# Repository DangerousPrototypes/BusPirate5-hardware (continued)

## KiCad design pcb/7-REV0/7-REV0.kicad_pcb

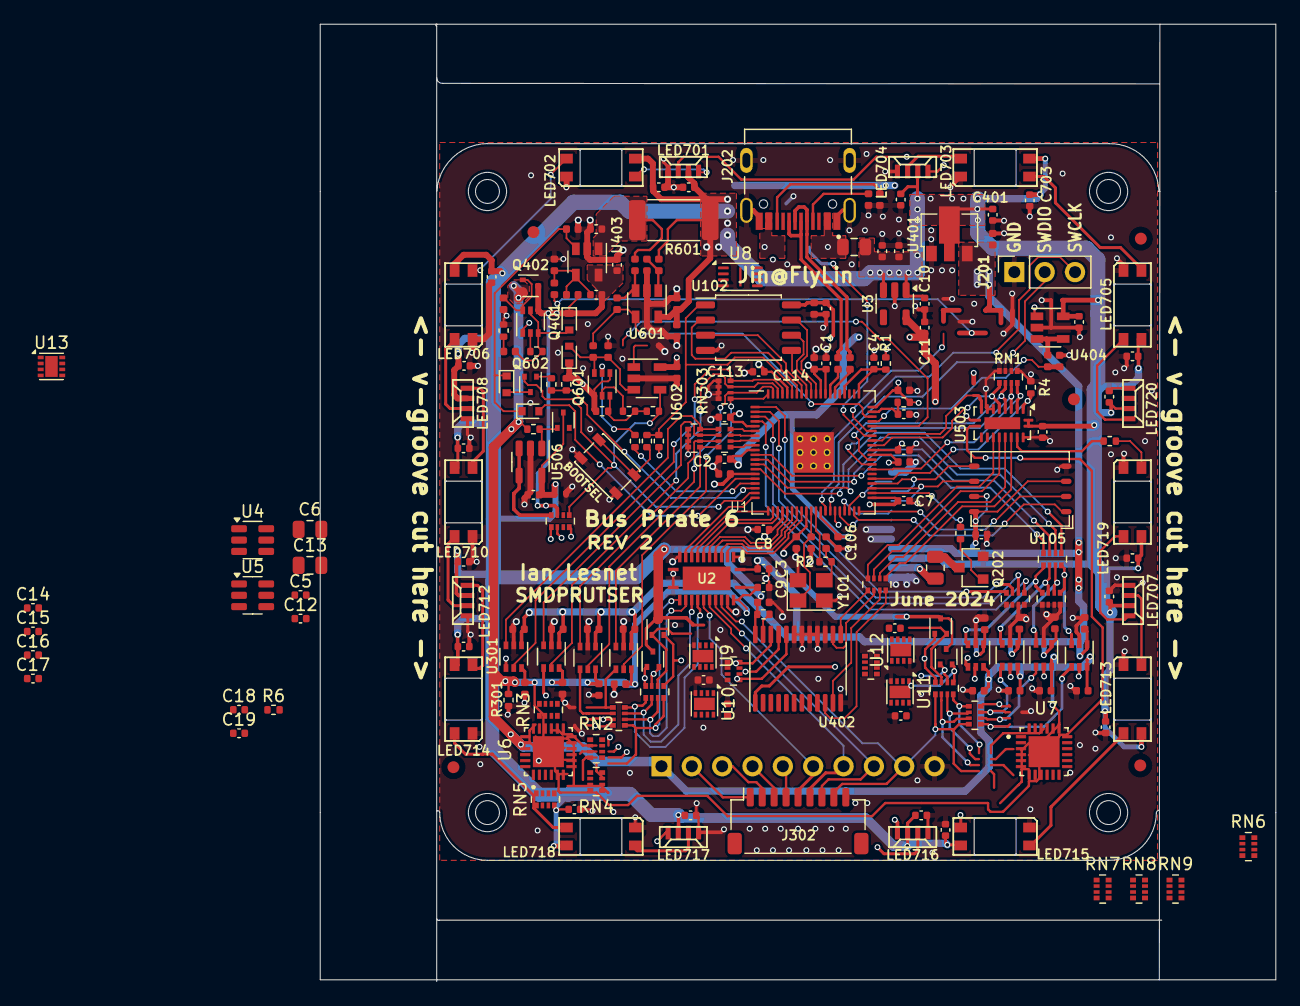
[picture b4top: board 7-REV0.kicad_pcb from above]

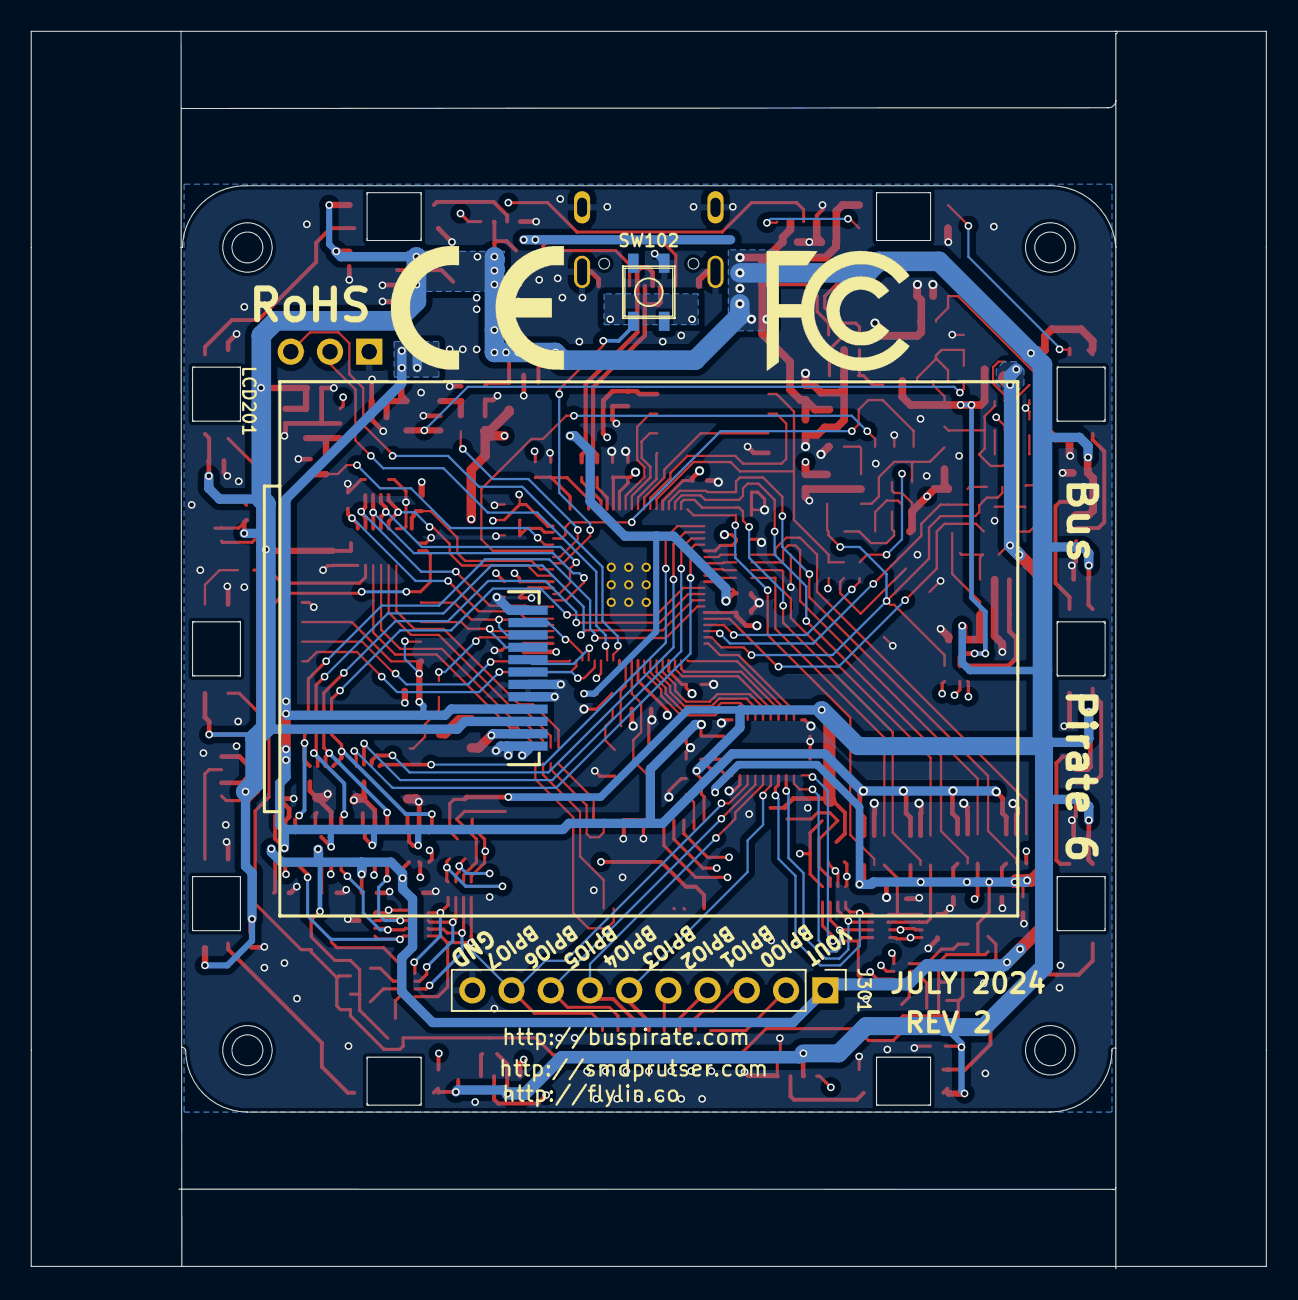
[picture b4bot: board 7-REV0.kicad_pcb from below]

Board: 4 copper layers, 80.0 x 80.0 mm, 232 parts (5 on the bottom side), 210 nets.

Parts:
C1, C2, C3, C5, C7, C8, C9, C12, C14, C15, C16, C17, C18, C103, C110, C111, C112, C113, C114, C115, C116, C117, C118, C121, C301, C302, C303, C304, C305, C306, C307, C308, C309, C310, C311, C312, C313, C314, C315, C316, C403, C406, C503, C506, C507, C508, C509, C510, C602, C605, C701, C702, C703, C704, C705, C706, C707, C708, C710, C712, C713, C714, C715, C716, C717, C718, C719, C720: 0.1uF; C_0402_1005Metric
C4, C19, C104, C109, C601: 2.2uF; C_0402_1005Metric
C6, C13: 10uF; C_0805_2012Metric
C10, C11, C201, C202, C401, C402, C404, C407: 4.7uF; C_0402_1005Metric
C105, C106: 15pF; C_0402_1005Metric
C408: 120pF; C_0402_1005Metric
C603: DNF; C_0402_1005Metric
D401, D601, D602, D603: 1N4148WT; D_SOD-523
D500, D501, D502, D503, D504: BAS40T-05; SOT-523
FID1, FID2, FID3, FID4, FID5: Fiducial; Fiducial_1mm_Mask2mm
H1, H2, H3, H4: MountingHole; MountingHole_3.2mm_M3
J201: Conn_01x03; PinSocket_1x03_P2.54mm_Vertical
J202: TYPE-C-31-M-12; HRO_TYPE-C-31-M-12
J301: Conn_01x10; PinHeader_1x10_P2.54mm_Vertical
J302: Conn_01x09; JST_SH_SM09B-SRSS-TB_1x09-1MP_P1.00mm_Horizontal
L201: CBW201209U300T; L_0805_2012Metric
LCD201: TFT_20_QT200H1201
LED701, LED704, LED707, LED708, LED712, LED716, LED717, LED720: SK6812-side-a_b
LED702, LED703, LED705, LED706, LED710, LED713, LED714, LED715, LED718, LED719: SK6812-mini-e
Q202: MMBT7002K; SOT-23
Q401: BCM857; SOT-363_SC-70-6
Q402, Q602: BC2301T 2.8A; SOT-523
Q601: MMDT3906; SOT-363_SC-70-6
R1: 10R; R_0402_1005Metric
R2, R101, R502, R602, R603: 1K; R_0402_1005Metric
R4, R6, R319, R401, R412: 100K; R_0402_1005Metric
R102: DNF; R_0402_1005Metric
R103, R208, R608, R612: 200R; R_0402_1005Metric
R201, R204: 5.1K; R_0402_1005Metric
R202, R203: 22R; R_0402_1005Metric
R209: 33R; R_0805_2012Metric
R301, R406, R407, R410, R606, R609, R610, R611, R613: 10K; R_0402_1005Metric
R320: 510R; R_0402_1005Metric
R403: 102K; R_0402_1005Metric
R404: 133K; R_0402_1005Metric
R405, R408, R409, R604, R605: 33K; R_0402_1005Metric
R601: 0R2; R_2512_6332Metric_Pad1.40x3.35mm_HandSolder
RN1, RN302, RN303, RN307, RN308, RN317, RN318: 100K; R_Array_Convex_4x0402
RN2, RN8: 1M; R_Array_Convex_4x0402
RN3, RN9: 10K; R_Array_Convex_4x0402
RN4, RN7: 4.7K; R_Array_Convex_4x0402
RN5, RN6: 2.2K; R_Array_Convex_4x0402
RN301, RN306: 330R; R_Array_Convex_4x0402
RN305, RN309: 120R; R_Array_Convex_4x0402
RN315, RN400, RN401, RN402: 510R; R_Array_Convex_4x0402
SW101: TS3425BA 098 2.5H 250gf; SW_SPST_PTS810
SW102: TS3315A 250gf 025; GT-TC026X-HXXX-LX
U1: RP2350B; qfn80
U2: 74LVC8T245BQ; NXP-DHVQFN24
U3: TLV74311PDBVR; SOT-23-5
U4, U5: MCP4725xxx-xCH; SOT-23-6
U6, U7: TCA6416RTWT; QFN50P400X400X80-25N
U8: APS6404L-3SQR-ZR; Winbond_USON-8-1EP_3x2mm_P0.5mm_EP0.2x1.6mm
U9, U10, U11, U12, U13: LM358_DFN; DFN-8-1EP_2x2mm_P0.5mm_EP1.05x1.75mm
U102: W25Q128JVSIQ; SOP-8_5.28x5.23mm_P1.27mm
U105: MT29F1G01ABAFDWB; U-PDFN-8
U301, U302, U303, U304, U305, U306, U307, U308: AiP74LVC1T45GC363.TR; SOT-363_SC-70-6
U401: ME6211A33PG-N; SOT-89-3
U402: CD4067; TSSOP-24_4.4x7.8mm_P0.65mm
U403: AP2127; SOT-23-5
U404, U506: LMV321; SOT-23-5
U503: 74HCT245BQ; DHVQFN-20-1EP_2.5x4.5mm_P0.5mm_EP1x3mm
U601: GS321A-TR; SOT-23-5
U602: GSV331-TR; SOT-23-5
Y101: ABM8-272-T3; Crystal_SMD_3225-4Pin_3.2x2.5mm
logo1: fcc_logo; logo_fcc
logo2: ce_logo; CE-Logo_11.2x8mm_SilkScreen

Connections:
+1V1: C2.1, C11.1, C117.1, C118.1, U1.10 (DVDD), U1.32 (DVDD), U1.51 (DVDD), U3.5 (VOUT)
+3V3: C1.1, C3.2, C5.1, C6.1, C7.1, C8.1, C12.1, C13.1, C15.2, C17.2, C18.1, C19.1, C103.1, C104.1, C110.1, C111.1, C112.1, C113.1, C114.1, C115.1, C116.1, C121.1, C301.2, C302.2, C303.2, C307.2, C308.2, C309.2, C313.2, C314.2, C402.1, C605.1, D601.1 (K), LCD201.4 (VCC), Q601.1 (E1), Q601.4 (E2), R1.1, R6.1, R102.1, R103.1, R609.1, R613.1, U1.5 (IOVDD), U1.15 (IOVDD), U1.24 (IOVDD), U1.29 (IOVDD), U1.35 (RUN), U1.41 (IOVDD), U1.50 (IOVDD), U1.60 (IOVDD), U1.68 (USB_OTP_VDD), U1.69 (QSPI_IOVDD), U1.76 (IOVDD), U2.1 (VCCA), U4.3 (VDD), U5.3 (VDD), U5.6 (A0), U6.23 (VCCI), U7.18 (ADDR), U7.23 (VCCI), U8.8 (VCC), U102.8 (VCC), U105.3 (WP/IO2), U105.7 (HOLD/IO3), U105.8 (VCC), U301.1 (VCCA), U302.1 (VCCA), U303.1 (VCCA), U304.1 (VCCA), U305.1 (VCCA), U306.1 (VCCA), U307.1 (VCCA), U308.1 (VCCA), U401.3 (VOUT), U602.5 (V+)
+VUSB: C10.1, C201.2, C202.2, C401.1, C403.2, C406.1, C503.2, C506.1, C507.2, C508.2, C509.2, C510.2, C601.1, C602.2, C701.2, C702.2, C703.2, C704.2, C705.2, C706.2, C707.2, C708.2, C710.2, C712.2, C713.2, C714.2, C715.2, C716.2, C717.2, C718.2, C719.2, C720.2, D500.3, D501.3, D502.3, D503.3, D504.3, L201.1, LCD201.3 (LED-A), LED701.3 (VDD), LED702.1 (VDD), LED703.1 (VDD), LED704.3 (VDD), LED705.1 (VDD), LED706.1 (VDD), LED707.3 (VDD), LED708.3 (VDD), LED710.1 (VDD), LED712.3 (VDD), LED713.1 (VDD), LED714.1 (VDD), LED715.1 (VDD), LED716.3 (VDD), LED717.3 (VDD), LED718.1 (VDD), LED719.1 (VDD), LED720.3 (VDD), R320.2, R601.1, R602.2, U3.1 (VIN), U3.3 (~SHDN), U9.8 (V+), U10.8 (V+), U11.8 (V+), U12.8 (V+), U401.2 (VIN), U402.24 (VCC), U404.5 (V+), U503.1 (A->B), U503.20 (VCC), U506.5 (V+), U601.5 (V+)
AMUX_OUT: R406.2, R407.2, U1.57 (GPIO46_ADC6)
AMUX_S0: RN315.4 (R1.1), U402.10 (S0)
AMUX_S0_3V3: RN1.8 (R1.8), U1.47 (GPIO38), U503.3 (A1)
AMUX_S1: RN315.3 (R1.1), U402.11 (S1)
AMUX_S1_3V3: RN1.7 (R1.8), U1.48 (GPIO39), U503.4 (A2)
AMUX_S2: RN315.2 (R1.1), U402.14 (S2)
AMUX_S2_3V3: RN1.6 (R1.8), U1.49 (GPIO40_ADC0), U503.5 (A3)
AMUX_S3: RN315.1 (R1.1), U402.13 (S3)
AMUX_S3_3V3: RN1.5 (R1.8), U1.52 (GPIO41_ADC1), U503.6 (A4)
BPIO0: J301.2, J302.1, RN6.4 (R1.1), RN7.4 (R1.1), RN8.1 (R1.1), RN9.1 (R1.1), RN305.1 (R1.1), RN318.8 (R1.8), U2.14 (B8)
BPIO1: J301.3, J302.2, RN6.3 (R1.1), RN7.3 (R1.1), RN8.2 (R1.1), RN9.2 (R1.1), RN305.2 (R1.1), RN318.7 (R1.8), U2.15 (B7)
BPIO2: J301.4, J302.3, RN6.2 (R1.1), RN7.2 (R1.1), RN8.3 (R1.1), RN9.3 (R1.1), RN305.3 (R1.1), RN318.6 (R1.8), U2.16 (B6)
BPIO3: J301.5, J302.4, RN6.1 (R1.1), RN7.1 (R1.1), RN8.4 (R1.1), RN9.4 (R1.1), RN305.4 (R1.1), RN318.5 (R1.8), U2.17 (B5)
BPIO4: J301.6, J302.5, RN2.1 (R1.1), RN3.1 (R1.1), RN4.4 (R1.1), RN5.4 (R1.1), RN309.1 (R1.1), RN317.8 (R1.8), U2.18 (B4)
BPIO5: J301.7, J302.6, RN2.2 (R1.1), RN3.2 (R1.1), RN4.3 (R1.1), RN5.3 (R1.1), RN309.2 (R1.1), RN317.7 (R1.8), U2.19 (B3)
BPIO6: J301.8, J302.7, RN2.3 (R1.1), RN3.3 (R1.1), RN4.2 (R1.1), RN5.2 (R1.1), RN309.3 (R1.1), RN317.6 (R1.8), U2.20 (B2)
BPIO7: J301.9, J302.8, RN2.4 (R1.1), RN3.4 (R1.1), RN4.1 (R1.1), RN5.1 (R1.1), RN309.4 (R1.1), RN317.5 (R1.8), U2.21 (B1)
BUFDIR0: RN303.8 (R1.8), U1.77 (GPIO0), U301.5 (DIR)
BUFDIR1: RN303.7 (R1.8), U1.78 (GPIO1), U302.5 (DIR)
BUFDIR2: RN303.6 (R1.8), U1.79 (GPIO2), U303.5 (DIR)
BUFDIR3: RN303.5 (R1.8), U1.80 (GPIO3), U304.5 (DIR)
BUFDIR4: RN308.8 (R1.8), U1.1 (GPIO4), U305.5 (DIR)
BUFDIR5: RN308.7 (R1.8), U1.2 (GPIO5), U306.5 (DIR)
BUFDIR6: RN308.6 (R1.8), U1.3 (GPIO6), U307.5 (DIR)
BUFDIR7: RN308.5 (R1.8), U1.4 (GPIO7), U308.5 (DIR)
BUFIO0: RN301.8 (R1.8), U1.6 (GPIO8)
BUFIO1: RN301.7 (R1.8), U1.7 (GPIO9)
BUFIO2: RN301.6 (R1.8), U1.8 (GPIO10)
BUFIO3: RN301.5 (R1.8), U1.9 (GPIO11)
BUFIO4: RN306.8 (R1.8), U1.11 (GPIO12)
BUFIO5: RN306.7 (R1.8), U1.12 (GPIO13)
BUFIO6: RN306.6 (R1.8), U1.13 (GPIO14)
BUFIO7: RN306.5 (R1.8), U1.14 (GPIO15)
BUTTONS: SW102.1, U1.54 (GPIO43_ADC3)
CURRENT_ADJ_MCU: U4.1 (VOUT), U602.1 (+)
CURRENT_DETECT: Q602.2 (S), R610.2, RN402.5 (R1.8), U1.19 (GPIO19), U602.4
CURRENT_EN: R612.2, R613.2, U1.18 (GPIO18)
CURRENT_EN_OVERRIDE: D603.2 (A), U1.16 (GPIO16)
CURRENT_RESET: R611.1, U1.17 (GPIO17)
CURRENT_SENSE: R605.1, R606.2, U1.58 (GPIO47_ADC7), U601.4
DISPLAY_BACKLIGHT: R208.1, U1.42 (GPIO33)
DISPLAY_CS: LCD201.8 (CS), U1.37 (GPIO29)
DISPLAY_DP: LCD201.7 (WR/SPI_A0), U1.36 (GPIO28)
DISPLAY_LED-K: LCD201.2 (LED-K), R209.2
DISPLAY_RESET: LCD201.11 (RESET), U1.38 (GPIO30)
FLASH_CS: U1.39 (GPIO31), U105.1 (CS)
GND: C1.2, C2.2, C3.1, C4.2, C5.2, C6.2, C7.2, C8.2, C9.2, C10.2, C11.2, C12.2, C13.2, C14.1, C15.1, C16.1, C17.1, C18.2, C19.2, C103.2, C104.2, C105.2, C106.2, C109.2, C110.2, C111.2, C112.2, C113.2, C114.2, C115.2, C116.2, C117.2, C118.2, C121.2, C201.1, C202.1, C301.1, C302.1, C303.1, C304.2, C305.2, C306.2, C307.1, C308.1, C309.1, C310.2, C311.2, C312.2, C313.1, C314.1, C315.2, C316.2, C401.2, C402.2, C403.1, C404.2, C406.2, C407.2, C503.1, C506.2, C507.1, C508.1, C509.1, C510.1, C601.2, C602.1, C603.1, C605.2, C701.1, C702.1, C703.1, C704.1, C705.1, C706.1, C707.1, C708.1, C710.1, C712.1, C713.1, C714.1, C715.1, C716.1, C717.1, C718.1, C719.1, C720.1, J201.1, J202.A1B12 (GND), J202.B1A12 (GND), J202.S1 (SHIELD), J202.S2 (SHIELD), J202.S3 (SHIELD), J202.S4 (SHIELD), J301.10, J302.9, LCD201.1 (GND), LCD201.5 (GND), LCD201.6 (GND), LCD201.12 (GND), LED701.1 (VSS), LED702.3 (VSS), LED703.3 (VSS), LED704.1 (VSS), LED705.3 (VSS), LED706.3 (VSS), LED707.1 (VSS), LED708.1 (VSS), LED710.3 (VSS), LED712.1 (VSS), LED713.3 (VSS), LED714.3 (VSS), LED715.3 (VSS), LED716.1 (VSS), LED717.1 (VSS), LED718.3 (VSS), LED719.3 (VSS), LED720.1 (VSS), Q202.2 (S), R4.1, R201.1, R204.1, R301.2, R401.2, R405.2, R407.1, R409.2, R412.2, R604.1, RN1.1 (R1.1), RN1.2 (R1.1), RN1.3 (R1.1), RN1.4 (R1.1), RN302.1 (R1.1), RN302.2 (R1.1), RN302.3 (R1.1), RN302.4 (R1.1), RN303.1 (R1.1), RN303.2 (R1.1), RN303.3 (R1.1), RN303.4 (R1.1), RN307.1 (R1.1), RN307.2 (R1.1), RN307.3 (R1.1), RN307.4 (R1.1), RN308.1 (R1.1), RN308.2 (R1.1), RN308.3 (R1.1), RN308.4 (R1.1), SW101.2 (B), SW102.4, U1.81 (GND), U2.2 (DIR), U2.11 (GND), U2.12 (GND), U2.13 (GND), U2.22 (~OE), U3.2 (GND), U4.2 (VSS), U4.6 (A0), U5.2 (VSS), U6.9 (GND), U6.18 (ADDR), U7.9 (GND), U8.4 (VSS), U9.4 (V-), U10.4 (V-), U11.4 (V-), U12.4 (V-), U102.4 (VSS), U105.4 (VSS), U301.2 (GND), U302.2 (GND), U303.2 (GND), U304.2 (GND), U305.2 (GND), U306.2 (GND), U307.2 (GND), U308.2 (GND), U401.1 (GND), U402.12 (GND), U402.15 (~E), U402.16 (I15), U402.17 (I14), U402.18 (I13), U402.19 (I12), U403.2 (GND), U404.2 (V-), U503.7 (A5), U503.8 (A6), U503.9 (A7), U503.10 (GND), U503.19 (CE), U506.2 (V-), U601.2 (V-), U602.2 (V-), Y101.2, Y101.4
I2C_RESET: U6.24 (~RESET), U7.24 (~RESET)
I2C_SCL: U4.5 (SCL), U5.5 (SCL), U6.19 (SCL), U7.19 (SCL)
I2C_SDA: U4.4 (SDA), U5.4 (SDA), U6.20 (SDA), U7.20 (SDA)
LA_BPIO0: U1.20 (GPIO20), U2.10 (A8)
LA_BPIO1: U1.21 (GPIO21), U2.9 (A7)
LA_BPIO2: U1.22 (GPIO22), U2.8 (A6)
LA_BPIO3: U1.23 (GPIO23), U2.7 (A5)
LA_BPIO4: U1.25 (GPIO24), U2.6 (A4)
LA_BPIO5: U1.26 (GPIO25), U2.5 (A3)
LA_BPIO6: U1.27 (GPIO26), U2.4 (A2)
LA_BPIO7: U1.28 (GPIO27), U2.3 (A1)
LEDS_CDO: R502.1, U503.18 (B0)
MUX_BPIO0: RN401.5 (R1.8), U9.6 (-), U9.7
MUX_BPIO1: RN401.6 (R1.8), U9.1, U9.2 (-)
MUX_BPIO2: RN401.7 (R1.8), U10.1, U10.2 (-)
MUX_BPIO3: RN401.8 (R1.8), U10.6 (-), U10.7
MUX_BPIO4: RN400.5 (R1.8), U11.6 (-), U11.7
MUX_BPIO5: RN400.6 (R1.8), U11.1, U11.2 (-)
MUX_BPIO6: RN400.7 (R1.8), U12.1, U12.2 (-)
MUX_BPIO7: RN400.8 (R1.8), U12.6 (-), U12.7
MUX_VREF_VOUT: RN402.8 (R1.8), U506.3 (-), U506.4
unnamed: C106.1, R2.1, Y101.3
unnamed: D401.2 (A), Q401.3 (C2), Q401.5 (B2), R408.2, R410.2
unnamed: C603.2, D601.2 (A), Q601.3 (C2), R606.1, U602.3 (-)
unnamed: D602.2 (A), Q602.3 (D)
unnamed: J202.A5 (CC1), R201.2
unnamed: J202.B5 (CC2), R204.2
unnamed: J202.A4B9 (VBUS), J202.B4A9 (VBUS), L201.2
unnamed: LED701.4 (DI), LED702.2 (DO)
unnamed: LED701.2 (DO), LED704.4 (DI)
unnamed: LED702.4 (DI), LED706.2 (DO)
unnamed: LED703.4 (DI), LED704.2 (DO)
unnamed: LED703.2 (DO), LED705.4 (DI)
unnamed: LED705.2 (DO), LED720.4 (DI)
unnamed: LED706.4 (DI), LED708.2 (DO)
unnamed: LED707.4 (DI), LED719.2 (DO)
unnamed: LED707.2 (DO), LED713.4 (DI)
unnamed: LED708.4 (DI), LED710.2 (DO)
unnamed: LED710.4 (DI), LED712.2 (DO)
unnamed: LED712.4 (DI), LED714.2 (DO)
unnamed: LED713.2 (DO), LED715.4 (DI)
unnamed: LED714.4 (DI), LED718.2 (DO)
unnamed: LED715.2 (DO), LED716.4 (DI)
unnamed: LED716.2 (DO), LED717.4 (DI)
unnamed: LED717.2 (DO), LED718.4 (DI)
unnamed: LED719.4 (DI), R502.2
unnamed: Q202.3 (D), R209.1
unnamed: Q202.1 (G), R208.2
unnamed: Q401.2 (B1), R410.1
unnamed: Q401.6 (C1), Q402.1 (G), R412.1
unnamed: Q601.2 (B1), R611.2
unnamed: Q601.6 (C1), R608.2, R609.2, R610.1
unnamed: Q601.5 (B2), R608.1
unnamed: Q602.1 (G), R612.1
unnamed: R408.1, R409.1
unnamed: RN2.8 (R1.8), U6.13
unnamed: RN2.7 (R1.8), U6.12
unnamed: RN2.6 (R1.8), U6.11
unnamed: RN2.5 (R1.8), U6.10
unnamed: RN3.8 (R1.8), U6.17
unnamed: RN3.7 (R1.8), U6.16
unnamed: RN3.6 (R1.8), U6.15
unnamed: RN3.5 (R1.8), U6.14
unnamed: RN4.8 (R1.8), U6.5 (P04)
unnamed: RN4.7 (R1.8), U6.6 (P05)
unnamed: RN4.6 (R1.8), U6.7 (P06)
unnamed: RN4.5 (R1.8), U6.8 (P07)
unnamed: RN5.8 (R1.8), U6.1 (P00)
unnamed: RN5.7 (R1.8), U6.2 (P01)
unnamed: RN5.6 (R1.8), U6.3 (P02)
unnamed: RN5.5 (R1.8), U6.4 (P03)
unnamed: RN6.8 (R1.8), U7.1 (P00)
unnamed: RN6.7 (R1.8), U7.2 (P01)
unnamed: RN6.6 (R1.8), U7.3 (P02)
unnamed: RN6.5 (R1.8), U7.4 (P03)
unnamed: RN7.8 (R1.8), U7.5 (P04)
unnamed: RN7.7 (R1.8), U7.6 (P05)
unnamed: RN7.6 (R1.8), U7.7 (P06)
unnamed: RN7.5 (R1.8), U7.8 (P07)
unnamed: RN8.8 (R1.8), U7.13
unnamed: RN8.7 (R1.8), U7.12
unnamed: RN8.6 (R1.8), U7.11
unnamed: RN8.5 (R1.8), U7.10
unnamed: RN9.8 (R1.8), U7.17
unnamed: RN9.7 (R1.8), U7.16
unnamed: RN9.6 (R1.8), U7.15
unnamed: RN9.5 (R1.8), U7.14
unnamed: RN301.1 (R1.1), RN302.8 (R1.8), U301.3 (A)
unnamed: RN301.2 (R1.1), RN302.7 (R1.8), U302.3 (A)
unnamed: RN301.3 (R1.1), RN302.6 (R1.8), U303.3 (A)
unnamed: RN301.4 (R1.1), RN302.5 (R1.8), U304.3 (A)
unnamed: RN305.8 (R1.8), U301.4 (B)
unnamed: RN305.7 (R1.8), U302.4 (B)
unnamed: RN305.6 (R1.8), U303.4 (B)
unnamed: RN305.5 (R1.8), U304.4 (B)
unnamed: RN306.1 (R1.1), RN307.8 (R1.8), U305.3 (A)
unnamed: RN306.2 (R1.1), RN307.7 (R1.8), U306.3 (A)
unnamed: RN306.3 (R1.1), RN307.6 (R1.8), U307.3 (A)
unnamed: RN306.4 (R1.1), RN307.5 (R1.8), U308.3 (A)
unnamed: RN309.8 (R1.8), U305.4 (B)
unnamed: RN309.7 (R1.8), U306.4 (B)
unnamed: RN309.6 (R1.8), U307.4 (B)
unnamed: RN309.5 (R1.8), U308.4 (B)
unnamed: RN315.8 (R1.8), U503.14 (B4)
unnamed: RN315.7 (R1.8), U503.15 (B3)
unnamed: RN315.6 (R1.8), U503.16 (B2)
unnamed: RN315.5 (R1.8), U503.17 (B1)
unnamed: D502.2, RN317.1 (R1.1), U11.5 (+)
unnamed: D502.1, RN317.2 (R1.1), U11.3 (+)
unnamed: D501.2, RN317.3 (R1.1), U12.3 (+)
unnamed: D501.1, RN317.4 (R1.1), U12.5 (+)
unnamed: D504.2, RN318.1 (R1.1), U9.5 (+)
unnamed: D504.1, RN318.2 (R1.1), U9.3 (+)
unnamed: D503.2, RN318.3 (R1.1), U10.3 (+)
unnamed: D503.1, RN318.4 (R1.1), U10.5 (+)
unnamed: RN400.1 (R1.1), U402.9 (I0)
unnamed: RN400.2 (R1.1), U402.8 (I1)
unnamed: RN400.3 (R1.1), U402.7 (I2)
unnamed: RN400.4 (R1.1), U402.6 (I3)
unnamed: RN401.1 (R1.1), U402.5 (I4)
unnamed: RN401.2 (R1.1), U402.4 (I5)
unnamed: RN401.3 (R1.1), U402.3 (I6)
unnamed: RN401.4 (R1.1), U402.2 (I7)
unnamed: RN402.1 (R1.1), U402.20 (I11)
unnamed: RN402.2 (R1.1), U402.21 (I10)
unnamed: RN402.4 (R1.1), U402.22 (I9)
unnamed: R101.2, SW101.1 (A)
unnamed: C109.1, R103.2, U1.59 (ADC_AVDD)
unnamed: C4.1, R1.2, U1.61 (VREG_AVDD), U1.64 (VREG_VIN)
unnamed: C105.1, U1.30 (XIN), Y101.1
unnamed: R2.2, U1.31 (XOUT)
unnamed: U402.1 (COM), U404.1 (+)
unnamed: R320.1, U402.23 (I8)
unnamed: C408.2, R403.2, R404.2, R405.1, U403.4 (ADJ)
unnamed: R406.1, U404.3 (-), U404.4
unnamed: D500.1, R319.1, U506.1 (+)
unnamed: R602.1, R604.2, U601.1 (+)
unnamed: R603.1, R605.2, U601.3 (-)
QSPI_SCLK: U1.71 (QSPI_SCLK), U8.6 (CLK), U102.6 (CLK)
QSPI_SD0: U1.72 (QSPI_SD0), U8.5 (DI), U102.5 (DI)
QSPI_SD1: U1.74 (QSPI_SD1), U8.2 (DO), U102.2 (DO)
QSPI_SD2: U1.73 (QSPI_SD2), U8.3 (WP), U102.3 (WP)
QSPI_SD3: U1.70 (QSPI_SD3), U8.7 (HOLD), U102.7 (HOLD)
QSPI_SS: R101.1, R102.2, U1.75 (QSPI_SS), U102.1 (CS)
QSPI_SS_2: R6.2, U8.1 (CS)
RGB_CDO: R4.2, U1.45 (GPIO36), U503.2 (A0)
SPI_CDI: U1.40 (GPIO32), U105.2 (SO/IO1)
SPI_CDO: LCD201.10 (SPI_SDA), U1.44 (GPIO35), U105.5 (SI/IO0)
SPI_CLK: LCD201.9 (RS/SPI_SCL), U1.43 (GPIO34), U105.6 (SCK)
SWCLK: J201.3, U1.33 (SWCLK)
SWDIO: J201.2, U1.34 (SWD)
USB_D+: R203.1, U1.67 (USB_DP)
USB_D-: R202.1, U1.66 (USB_DM)
USB_N: J202.A7 (DN1), J202.B7 (DN2), R202.2
USB_P: J202.A6 (DP1), J202.B6 (DP2), R203.2
VREF_VOUT: C9.1, C14.2, C16.2, C304.1, C305.1, C306.1, C310.1, C311.1, C312.1, C315.1, C316.1, J301.1, Q401.1 (E1), Q402.2 (S), R301.1, R319.2, U2.23 (VCCB), U2.24 (VCCB), U6.21 (VCCP), U7.21 (VCCP), U301.6 (VCCB), U302.6 (VCCB), U303.6 (VCCB), U304.6 (VCCB), U305.6 (VCCB), U306.6 (VCCB), U307.6 (VCCB), U308.6 (VCCB)
VREG_ADJ: R403.1, U5.1 (VOUT)
VREG_EN: D602.1 (K), D603.1 (K), R401.1, U403.3 (SHUTDOWN)
VREG_OUT: C407.1, C408.1, D401.1 (K), Q401.4 (E2), Q402.3 (D), R404.1, RN402.7 (R1.8), U403.5 (OUT)
VREG_VIN: C404.1, R601.2, R603.2, U403.1 (VIN)
